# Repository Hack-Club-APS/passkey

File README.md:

# Passkey
This passkey is made so that the user can login without using a password. Using the picokeys firmware for raspberry pi microcontrollers, it is pretty secure(FIDO2) and fun to use. Even though it has a small form factor, it carries one button and a white LED - enough for passwordless login and some custom HID stuff.  

view this project on [KiCanvas](http://kicanvas.org/?github=https://github.com/Hack-Club-APS/passkey/tree/main/aps_passkey_hardware)!  

## Bill Of Materials:
| Item             | Cost  | Note        |
|------------------|-------|-------------|
| PCB              | 2     | from jlcpcb |
| PCBA             | 44.31 |             |
| Shipping charges | 11.39 |             |
| Discount         | -9    |             |
| Total            | 48.70 | USD         |

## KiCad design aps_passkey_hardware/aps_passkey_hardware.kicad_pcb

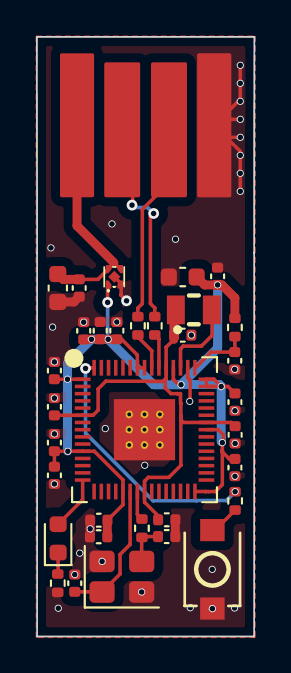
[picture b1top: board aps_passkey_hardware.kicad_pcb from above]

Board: 2 copper layers, 12.1 x 33.3 mm, 34 parts (0 on the bottom side), 17 nets.

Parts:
C1, C2, C3, C6, C18, C21: 4.7u; C_0402_1005Metric
C4, C5: 33p; C_0402_1005Metric
C7, C8, C9, C10, C11, C12, C13, C14, C15, C16, C17: 100n; C_0402_1005Metric
C19, C20: 10u; C_0603_1608Metric
D1: LED; LED_0603_1608Metric
J1: USB_A; USBPCB
L1: AOTA; IND-SMD_L2.0-W1.6_AOTA-B201610S3R3-101-T
R1: 33; R_0402_1005Metric
R2, R3: 27R; R_0402_1005Metric
R4, R5, R6: 1k; R_0402_1005Metric
SW1: SW_Push; SW-SMD_L3.9-W3.0-P4.45
U1: RP2350A-QFN60; RP2350A_QFN-60_EP_7.75x7.75_Pitch0.4mm
U2: TLV75512PDQNR; X2SON-4_L1.0-W1.0-P0.65-TL-EP
Y1: Crystal_GND24; Crystal_SMD_3225-4Pin_3.2x2.5mm

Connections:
+1V1: C1.1, C6.1, C7.1, C8.1, L1.2, U1.6 (DVDD), U1.23 (DVDD), U1.39 (DVDD), U1.50 (VREG_FB)
+3V3: C3.1, C9.1, C10.1, C11.1, C12.1, C13.1, C14.1, C15.1, C16.1, C17.1, C18.1, C19.1, R1.1, U1.1 (IOVDD), U1.11 (IOVDD), U1.20 (IOVDD), U1.30 (IOVDD), U1.38 (IOVDD), U1.44 (ADC_AVDD), U1.45 (IOVDD), U1.49 (VREG_VIN), U1.53 (USB_OTP_VDD), U1.54 (QSPI_IOVDD), U2.1 (OUT)
/TR+: R2.1, U1.52 (USB_DP)
/TR-: R3.1, U1.51 (USB_DM)
D+: J1.3 (D+), R2.2
D-: J1.2 (D-), R3.2
GND: C1.2, C2.2, C3.2, C4.2, C5.2, C6.2, C7.2, C8.2, C9.2, C10.2, C11.2, C12.2, C13.2, C14.2, C15.2, C16.2, C17.2, C18.2, C19.2, C20.2, C21.2, J1.4 (GND), R6.2, SW1.1, U1.47 (VREG_PGND), U1.61 (GND), U2.2 (GND), U2.5 (EP), Y1.2, Y1.4
unnamed: D1.2 (A), U1.15 (GPIO11)
unnamed: D1.1 (K), R6.1
unnamed: C20.1, C21.1, J1.1 (VBUS), U2.3 (EN), U2.4 (IN)
unnamed: R4.1, SW1.2
unnamed: C2.1, R1.2, U1.46 (VREG_AVDD)
unnamed: L1.1, U1.48 (VREG_LX)
unnamed: R5.2, U1.22 (XOUT)
QSPI_SS: R4.2, U1.60 (QSPI_SS)
XIN: C4.1, U1.21 (XIN), Y1.1
XOUT: C5.1, R5.1, Y1.3

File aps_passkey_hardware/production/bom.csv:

Designator,Footprint,Quantity,Value,LCSC Part #
"C1, C18, C2, C21, C3, C6",0402,6,4.7u,
"C10, C11, C12, C13, C14, C15, C16, C17, C7, C8, C9",0402,11,100n,
"C19, C20",0603,2,10u,
"C4, C5",0402,2,33p,
D1,0603,1,LED,
J1,USBPCB,1,USB_A,
L1,IND-SMD_L2.0-W1.6_AOTA-B201610S3R3-101-T,1,AOTA,C42411119
R1,0402,1,33,
"R2, R3",0402,2,27R,
"R4, R5, R6",0402,3,1k,
SW1,SW-SMD_L3.9-W3.0-P4.45,1,SW_Push,
U1,RP2350A_QFN-60_EP_7.75x7.75_Pitch0.4mm,1,RP2350A-QFN60,
U2,X2SON-4_L1.0-W1.0-P0.65-TL-EP,1,TLV75512PDQNR,C2867150
Y1,Crystal_SMD_3225-4Pin_3.2x2.5mm,1,Crystal_GND24,

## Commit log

2025-12-07 Hello World!
2025-12-07 schematic
2025-12-09 new design
2025-12-11 PCB Done
2025-12-24 added silkscreen+panelisation part
2025-12-24 fixed ground errors
2025-12-24 added BOM
2025-12-24 cart pic
2025-12-24 added README
2025-12-24 final changes
